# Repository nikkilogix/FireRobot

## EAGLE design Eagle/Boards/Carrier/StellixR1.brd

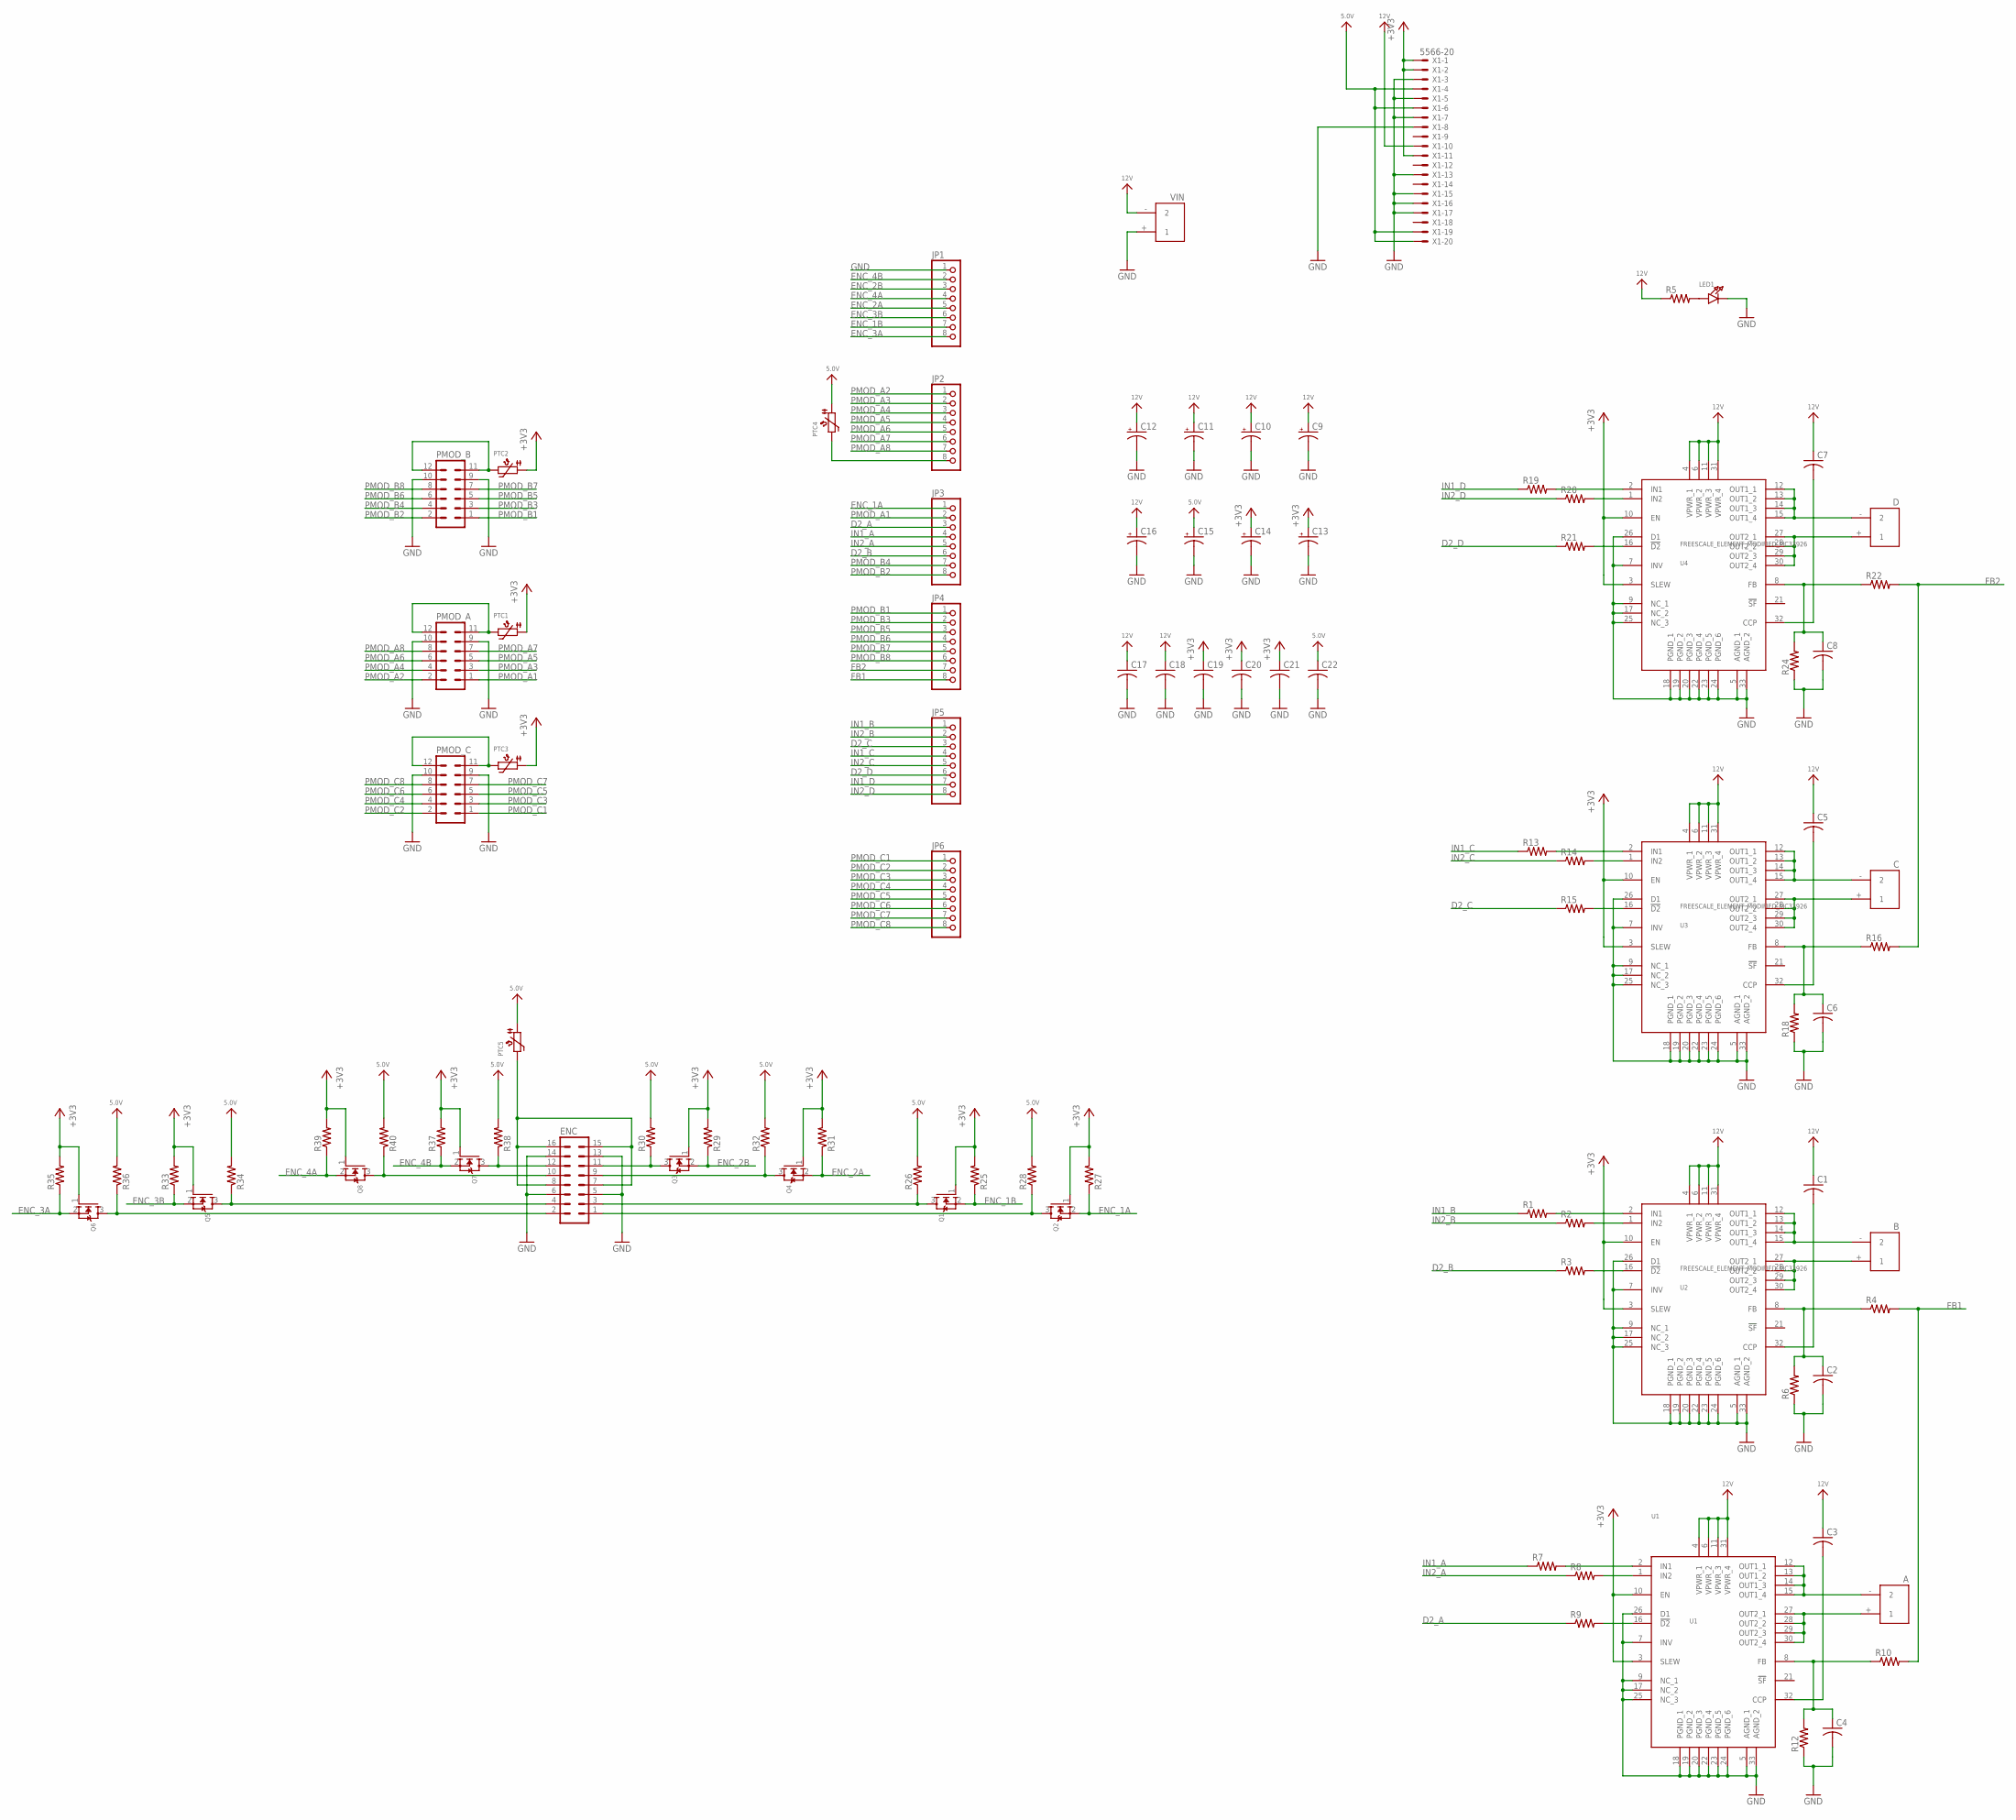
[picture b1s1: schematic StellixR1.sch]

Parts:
A: XT60_FEMALE
B: XT60_FEMALE
C: XT60_FEMALE
C1, C2, C3, C4, C5, C6, C7, C8, C17, C18, C19, C20, C21, C22: C-USC0805; C0805
C9, C10, C11, C12, C13, C14, C15, C16: CPOL-US153CLV-0605; 153CLV-0605
D: XT60_FEMALE
ENC: MA08-2
JP1, JP2, JP3, JP4, JP5, JP6: HEADER-1X8ROUND; 1X08_ROUND
LED1: LED0805_NOOUTLINE; CHIPLED_0805_NOOUTLINE
PMOD_A: MA06-2
PMOD_B: MA06-2
PMOD_C: MA06-2
PTC1, PTC2, PTC3, PTC4, PTC5: PTC1812
Q1, Q2, Q3, Q4, Q5, Q6, Q7, Q8: MOSFET-NWIDE; SOT23-WIDE
R1, R2, R3, R4, R5, R6, R7, R8, R9, R10, R12, R13, R14, R15, R16, R18, R19, R20, R21, R22, R24, R25, R26, R27, R28, R29, R30, R31, R32, R33, R34, R35, R36, R37, R38, R39, R40: R-US_R0805; R0805
U1: U1; FREESCALE_ELEMENT_MODIFIED_PQFN32_0P8_8X8_SLUG
U2, U3, U4: FREESCALE_ELEMENT_MODIFIED_MC33926; FREESCALE_ELEMENT_MODIFIED_PQFN32_0P8_8X8_SLUG
VIN: XT60_FEMALE
X1: 5566-20

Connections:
5.0V: C15.+, C22.1, PTC4.P$1 (1), PTC5.P$1 (1), R26.2, R28.2, R30.2, R32.2, R34.2, R36.2, R38.2, R40.2, X1.4, X1.6, X1.19, X1.20
12V: C1.1, C3.1, C5.1, C7.1, C9.+, C10.+, C11.+, C12.+, C16.+, C17.1, C18.1, R5.1, U1.4 (VPWR_1), U1.6 (VPWR_2), U1.11 (VPWR_3), U1.31 (VPWR_4), U2.4 (VPWR_1), U2.6 (VPWR_2), U2.11 (VPWR_3), U2.31 (VPWR_4), U3.4 (VPWR_1), U3.6 (VPWR_2), U3.11 (VPWR_3), U3.31 (VPWR_4), U4.4 (VPWR_1), U4.6 (VPWR_2), U4.11 (VPWR_3), U4.31 (VPWR_4), VIN.- (2), X1.10
+3V3: C13.+, C14.+, C19.1, C20.1, C21.1, PTC1.P$1 (1), PTC2.P$1 (1), PTC3.P$1 (1), Q1.1 (G), Q2.1 (G), Q3.1 (G), Q4.1 (G), Q5.1 (G), Q6.1 (G), Q7.1 (G), Q8.1 (G), R25.2, R27.2, R29.2, R31.2, R33.2, R35.2, R37.2, R39.2, U1.3 (SLEW), U1.10 (EN), U2.3 (SLEW), U2.10 (EN), U3.3 (SLEW), U3.10 (EN), U4.3 (SLEW), U4.10 (EN), X1.1, X1.2, X1.11
D2_A: JP3.3, R9.1
D2_B: JP3.6, R3.1
D2_C: JP5.3, R15.1
D2_D: JP5.6, R21.1
ENC_1A: JP3.1, Q2.2 (S), R27.1
ENC_1B: JP1.7, Q1.2 (S), R25.1
ENC_2A: JP1.5, Q4.2 (S), R31.1
ENC_2B: JP1.3, Q3.2 (S), R29.1
ENC_3A: JP1.8, Q6.2 (S), R35.1
ENC_3B: JP1.6, Q5.2 (S), R33.1
ENC_4A: JP1.4, Q8.2 (S), R39.1
ENC_4B: JP1.2, Q7.2 (S), R37.1
FB1: JP4.8, R4.2, R10.2
FB2: JP4.7, R16.2, R22.2
GND: C2.2, C4.2, C6.2, C8.2, C9.-, C10.-, C11.-, C12.-, C13.-, C14.-, C15.-, C16.-, C17.2, C18.2, C19.2, C20.2, C21.2, C22.2, ENC.5, ENC.6, ENC.13, ENC.14, JP1.1, LED1.C, PMOD_A.9, PMOD_A.10, PMOD_B.9, PMOD_B.10, PMOD_C.9, PMOD_C.10, R6.1, R12.1, R18.1, R24.1, U1.5 (AGND_1), U1.7 (INV), U1.9 (NC_1), U1.17 (NC_2), U1.18 (PGND_1), U1.19 (PGND_2), U1.20 (PGND_3), U1.22 (PGND_4), U1.23 (PGND_5), U1.24 (PGND_6), U1.25 (NC_3), U1.26 (D1), U1.33 (AGND_2), U2.5 (AGND_1), U2.7 (INV), U2.9 (NC_1), U2.17 (NC_2), U2.18 (PGND_1), U2.19 (PGND_2), U2.20 (PGND_3), U2.22 (PGND_4), U2.23 (PGND_5), U2.24 (PGND_6), U2.25 (NC_3), U2.26 (D1), U2.33 (AGND_2), U3.5 (AGND_1), U3.7 (INV), U3.9 (NC_1), U3.17 (NC_2), U3.18 (PGND_1), U3.19 (PGND_2), U3.20 (PGND_3), U3.22 (PGND_4), U3.23 (PGND_5), U3.24 (PGND_6), U3.25 (NC_3), U3.26 (D1), U3.33 (AGND_2), U4.5 (AGND_1), U4.7 (INV), U4.9 (NC_1), U4.17 (NC_2), U4.18 (PGND_1), U4.19 (PGND_2), U4.20 (PGND_3), U4.22 (PGND_4), U4.23 (PGND_5), U4.24 (PGND_6), U4.25 (NC_3), U4.26 (D1), U4.33 (AGND_2), VIN.+ (1), X1.3, X1.5, X1.7, X1.8, X1.13, X1.15, X1.16, X1.17
IN1_A: JP3.4, R7.1
IN1_B: JP5.1, R1.1
IN1_C: JP5.4, R13.1
IN1_D: JP5.7, R19.1
IN2_A: JP3.5, R8.1
IN2_B: JP5.2, R2.1
IN2_C: JP5.5, R14.1
IN2_D: JP5.8, R20.1
MOUTA: B.- (2), U2.12 (OUT1_1), U2.13 (OUT1_2), U2.14 (OUT1_3), U2.15 (OUT1_4)
MOUTB: B.+ (1), U2.27 (OUT2_1), U2.28 (OUT2_2), U2.29 (OUT2_3), U2.30 (OUT2_4)
unnamed: R3.2, U2.16 (!D2)
unnamed: JP2.8, PTC4.P$2 (2)
unnamed: PMOD_A.11, PMOD_A.12, PTC1.P$2 (2)
unnamed: R8.2, U1.1 (IN2)
unnamed: PMOD_C.11, PMOD_C.12, PTC3.P$2 (2)
unnamed: R2.2, U2.1 (IN2)
unnamed: R1.2, U2.2 (IN1)
unnamed: ENC.1, Q2.3 (D), R28.1
unnamed: ENC.4, Q5.3 (D), R34.1
unnamed: R7.2, U1.2 (IN1)
unnamed: PMOD_B.11, PMOD_B.12, PTC2.P$2 (2)
unnamed: C1.2, U2.32 (CCP)
unnamed: A.- (2), U1.12 (OUT1_1), U1.13 (OUT1_2), U1.14 (OUT1_3), U1.15 (OUT1_4)
unnamed: C2.1, R4.1, R6.2, U2.8 (FB)
unnamed: ENC.7, ENC.8, ENC.15, ENC.16, PTC5.P$2 (2)
unnamed: LED1.A, R5.2
unnamed: A.+ (1), U1.27 (OUT2_1), U1.28 (OUT2_2), U1.29 (OUT2_3), U1.30 (OUT2_4)
unnamed: C3.2, U1.32 (CCP)
unnamed: R9.2, U1.16 (!D2)
unnamed: C4.1, R10.1, R12.2, U1.8 (FB)
unnamed: R14.2, U3.1 (IN2)
unnamed: R13.2, U3.2 (IN1)
unnamed: C.- (2), U3.12 (OUT1_1), U3.13 (OUT1_2), U3.14 (OUT1_3), U3.15 (OUT1_4)
unnamed: C.+ (1), U3.27 (OUT2_1), U3.28 (OUT2_2), U3.29 (OUT2_3), U3.30 (OUT2_4)
unnamed: C5.2, U3.32 (CCP)
unnamed: R15.2, U3.16 (!D2)
unnamed: C6.1, R16.1, R18.2, U3.8 (FB)
unnamed: R20.2, U4.1 (IN2)
unnamed: R19.2, U4.2 (IN1)
unnamed: D.- (2), U4.12 (OUT1_1), U4.13 (OUT1_2), U4.14 (OUT1_3), U4.15 (OUT1_4)
unnamed: D.+ (1), U4.27 (OUT2_1), U4.28 (OUT2_2), U4.29 (OUT2_3), U4.30 (OUT2_4)
unnamed: C7.2, U4.32 (CCP)
unnamed: R21.2, U4.16 (!D2)
unnamed: C8.1, R22.1, R24.2, U4.8 (FB)
unnamed: ENC.3, Q1.3 (D), R26.1
unnamed: ENC.2, Q6.3 (D), R36.1
unnamed: ENC.11, Q3.3 (D), R30.1
unnamed: ENC.9, Q4.3 (D), R32.1
unnamed: ENC.12, Q7.3 (D), R38.1
unnamed: ENC.10, Q8.3 (D), R40.1
PMOD_A1: JP3.2, PMOD_A.1
PMOD_A2: JP2.1, PMOD_A.2
PMOD_A3: JP2.2, PMOD_A.3
PMOD_A4: JP2.3, PMOD_A.4
PMOD_A5: JP2.4, PMOD_A.5
PMOD_A6: JP2.5, PMOD_A.6
PMOD_A7: JP2.6, PMOD_A.7
PMOD_A8: JP2.7, PMOD_A.8
PMOD_B1: JP4.1, PMOD_B.1
PMOD_B2: JP3.8, PMOD_B.2
PMOD_B3: JP4.2, PMOD_B.3
PMOD_B4: JP3.7, PMOD_B.4
PMOD_B5: JP4.3, PMOD_B.5
PMOD_B6: JP4.4, PMOD_B.6
PMOD_B7: JP4.5, PMOD_B.7
PMOD_B8: JP4.6, PMOD_B.8
PMOD_C1: JP6.1, PMOD_C.1
PMOD_C2: JP6.2, PMOD_C.2
PMOD_C3: JP6.3, PMOD_C.3
PMOD_C4: JP6.4, PMOD_C.4
PMOD_C5: JP6.5, PMOD_C.5
PMOD_C6: JP6.6, PMOD_C.6
PMOD_C7: JP6.7, PMOD_C.7
PMOD_C8: JP6.8, PMOD_C.8

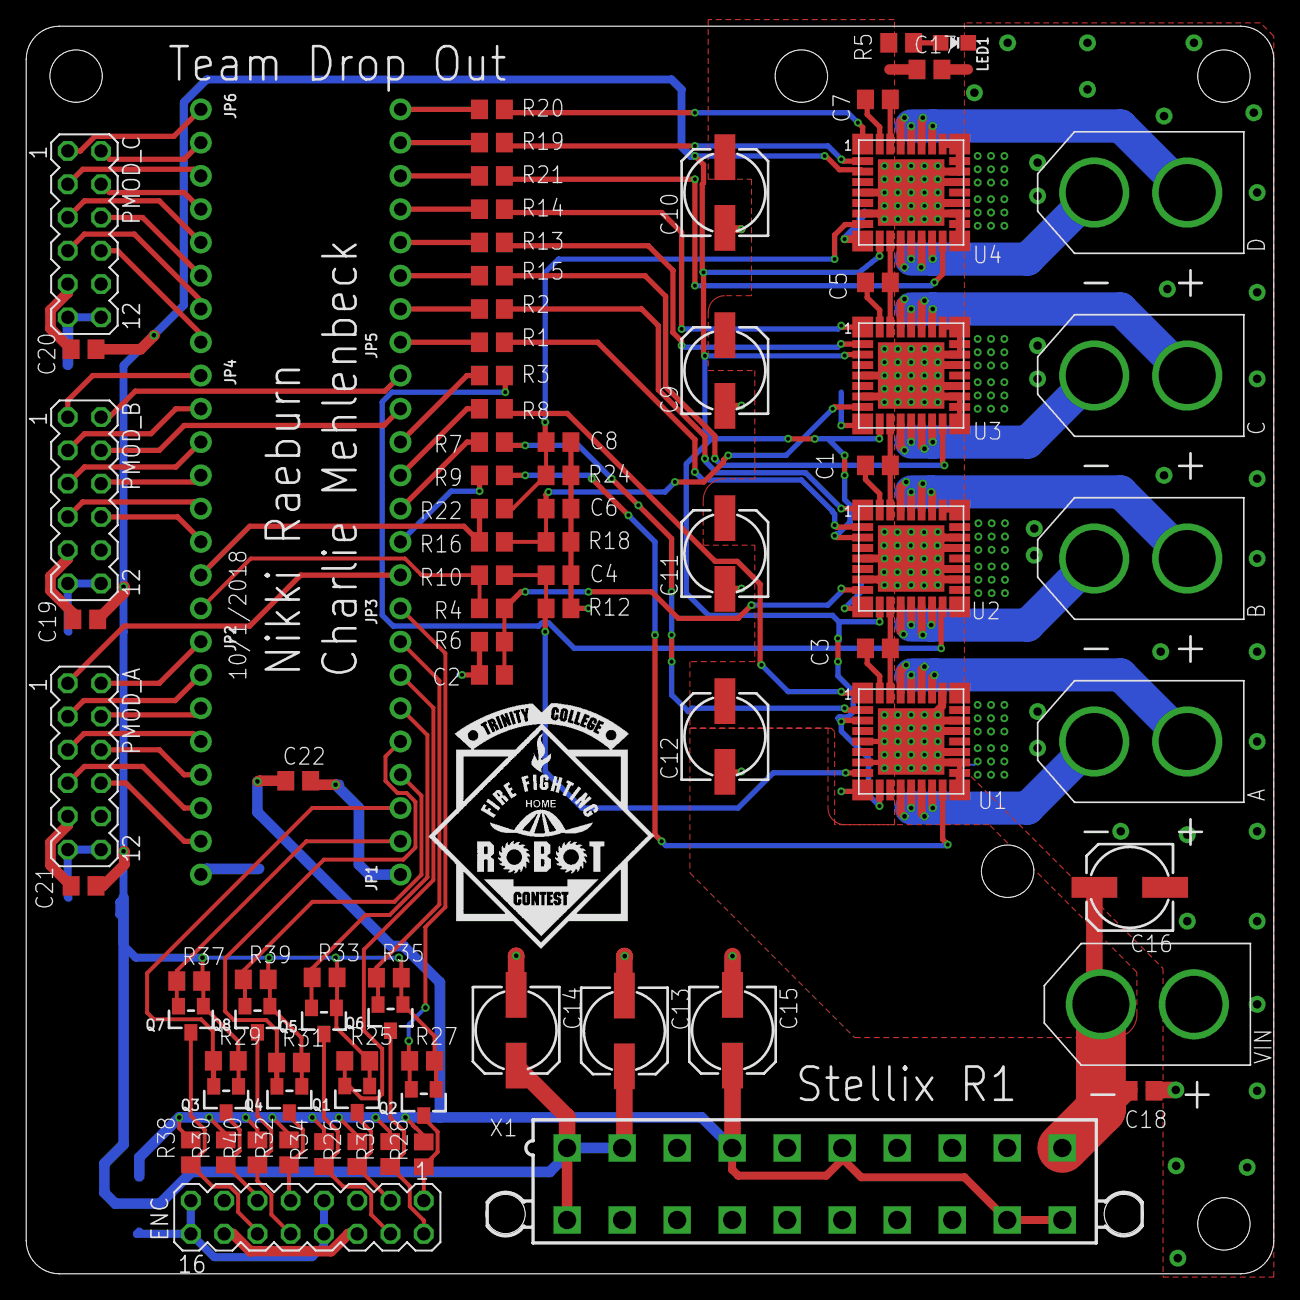
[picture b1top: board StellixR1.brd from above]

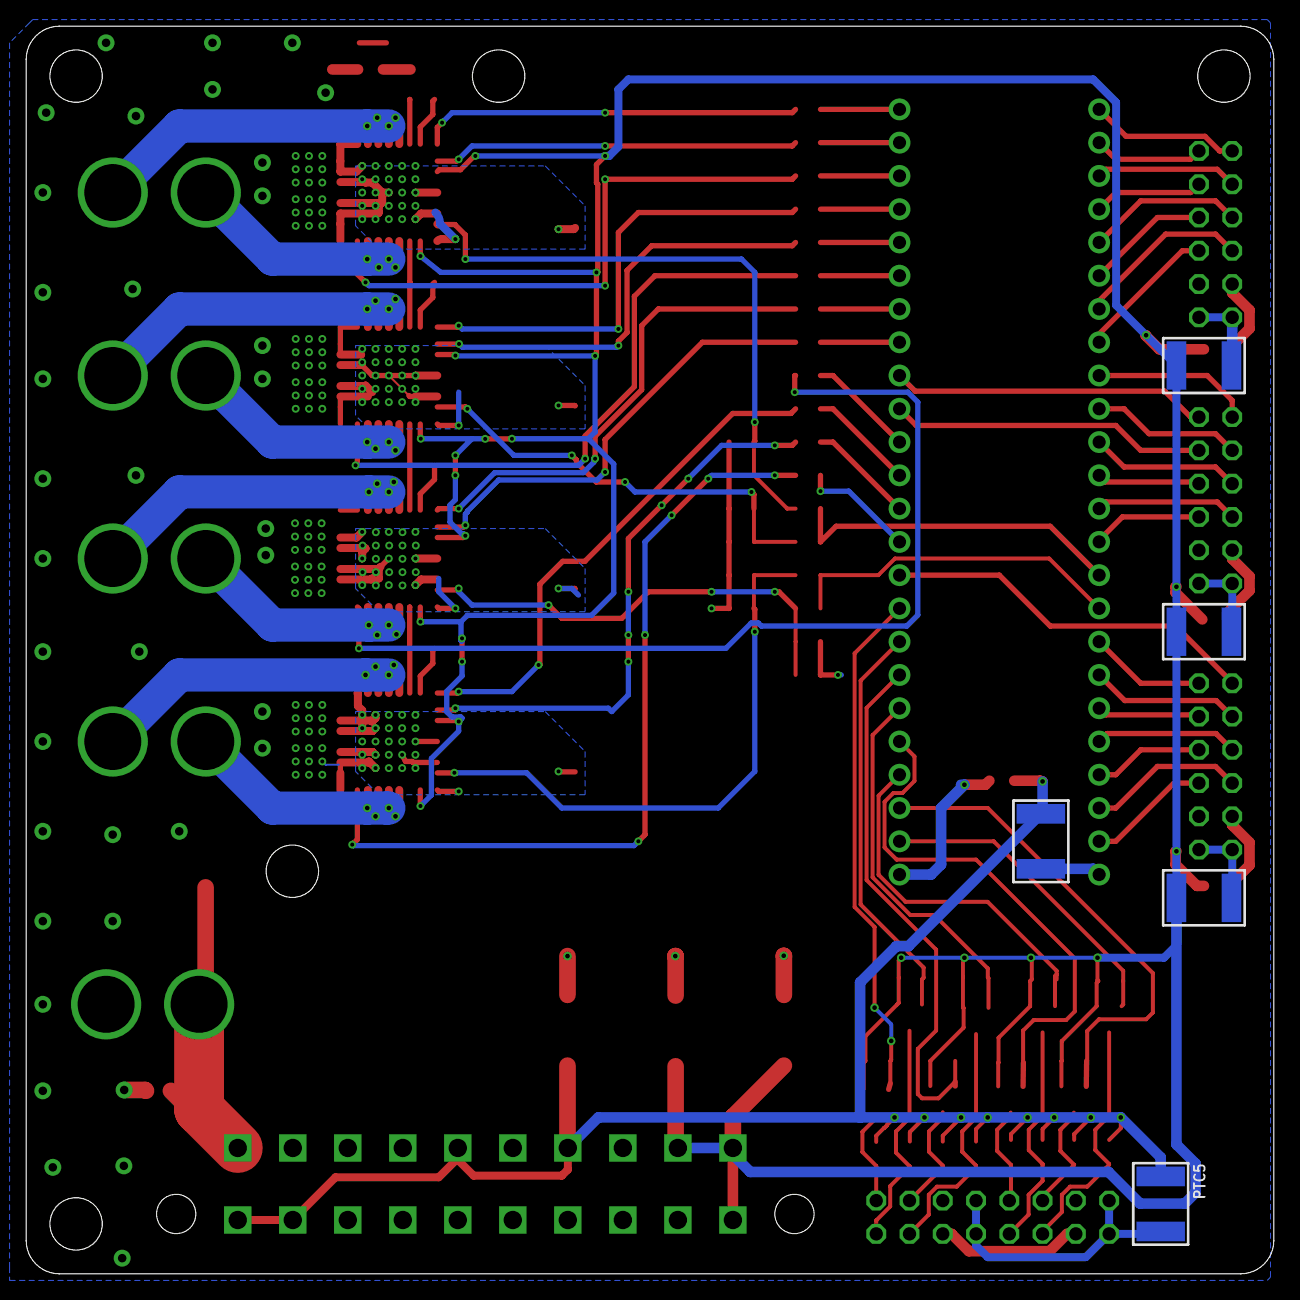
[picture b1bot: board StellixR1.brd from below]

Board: 2 copper layers, 95.2 x 95.2 mm, 93 parts (5 on the bottom side), 92 nets.

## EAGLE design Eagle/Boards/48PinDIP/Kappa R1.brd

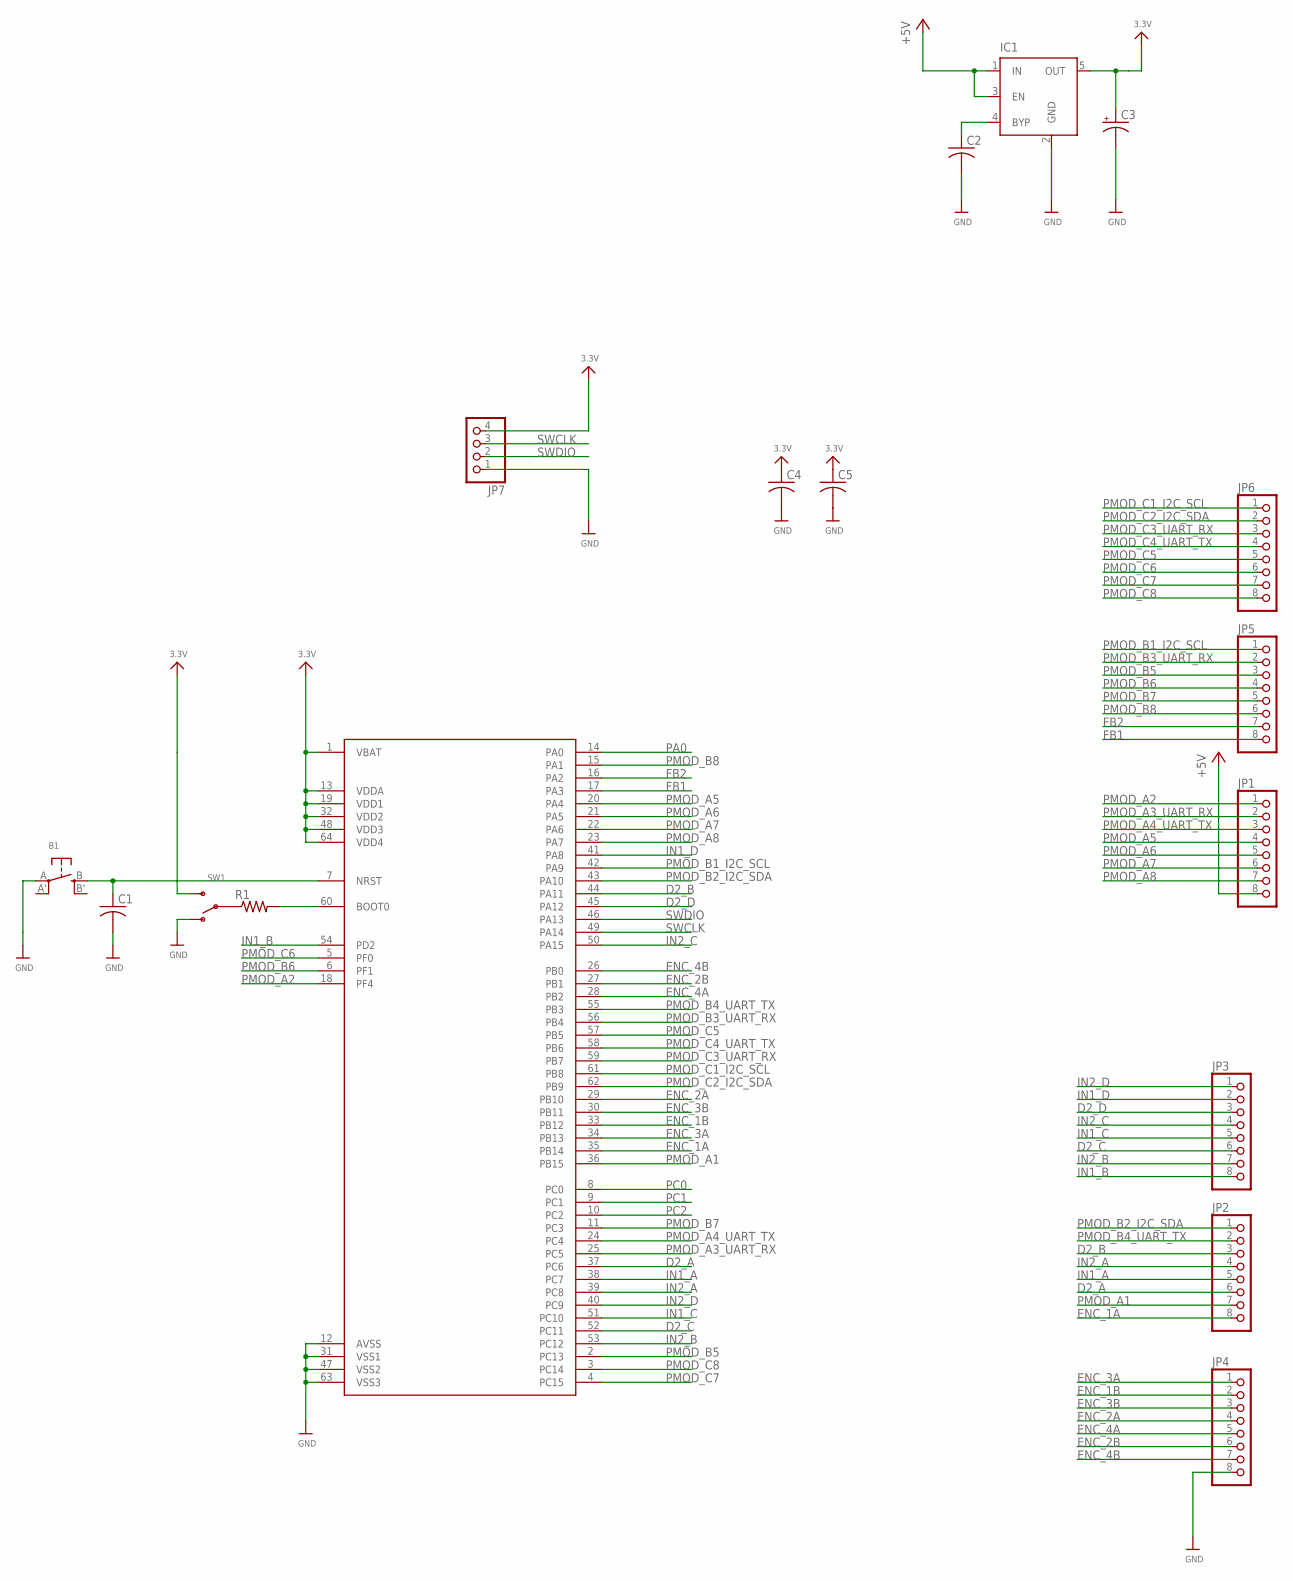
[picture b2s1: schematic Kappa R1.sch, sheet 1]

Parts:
B1: SWITCH_TACT_SMT4.6X2.8; BTN_KMR2_4.6X2.8
C1, C2: C-USC0805K; C0805K
C3: CPOL-USCT3216; CT3216
C4, C5: C-USC0805; C0805
IC1: MIC5219XX; SOT23-5
JP1, JP2, JP3, JP4, JP5, JP6: HEADER-1X8ROUND; 1X08_ROUND
JP7: HEADER-1X4ROUND; 1X04_ROUND
R1: R-US_R0805; R0805
SW1: SWITCH_SPDT; SPDT_SMT_SSSS811101
U$1: STM32F303; LQFP64

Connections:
3.3V: C3.- (+), C4.1, C5.1, IC1.5 (OUT), JP7.4, SW1.C (S), U$1.1 (VBAT), U$1.13 (VDDA), U$1.19 (VDD1), U$1.32 (VDD2), U$1.48 (VDD3), U$1.64 (VDD4)
+5V: IC1.1 (IN), IC1.3 (EN), JP1.8
D2_A: JP2.6, U$1.37 (PC6)
D2_B: JP2.3, U$1.44 (PA11)
D2_C: JP3.6, U$1.52 (PC11)
D2_D: JP3.3, U$1.45 (PA12)
ENC_1A: JP2.8, U$1.35 (PB14)
ENC_1B: JP4.2, U$1.33 (PB12)
ENC_2A: JP4.4, U$1.29 (PB10)
ENC_2B: JP4.6, U$1.27 (PB1)
ENC_3A: JP4.1, U$1.34 (PB13)
ENC_3B: JP4.3, U$1.30 (PB11)
ENC_4A: JP4.5, U$1.28 (PB2)
ENC_4B: JP4.7, U$1.26 (PB0)
FB1: JP5.8, U$1.17 (PA3)
FB2: JP5.7, U$1.16 (PA2)
GND: B1.A, C1.2, C2.2, C3.+ (-), C4.2, C5.2, IC1.2 (GND), JP4.8, JP7.1, SW1.A (O), U$1.12 (AVSS), U$1.31 (VSS1), U$1.47 (VSS2), U$1.63 (VSS3)
IN1_A: JP2.5, U$1.38 (PC7)
IN1_B: JP3.8, U$1.54 (PD2)
IN1_C: JP3.5, U$1.51 (PC10)
IN1_D: JP3.2, U$1.41 (PA8)
IN2_A: JP2.4, U$1.39 (PC8)
IN2_B: JP3.7, U$1.53 (PC12)
IN2_C: JP3.4, U$1.50 (PA15)
IN2_D: JP3.1, U$1.40 (PC9)
unnamed: R1.2, U$1.60 (BOOT0)
unnamed: B1.B (S), C1.1, U$1.7 (NRST)
unnamed: R1.1, SW1.B
unnamed: C2.1, IC1.4 (BYP)
PA0: U$1.14 (PA0)
PC0: U$1.8 (PC0)
PC1: U$1.9 (PC1)
PC2: U$1.10 (PC2)
PMOD_A1: JP2.7, U$1.36 (PB15)
PMOD_A2: JP1.1, U$1.18 (PF4)
PMOD_A3_UART_RX: JP1.2, U$1.25 (PC5)
PMOD_A4_UART_TX: JP1.3, U$1.24 (PC4)
PMOD_A5: JP1.4, U$1.20 (PA4)
PMOD_A6: JP1.5, U$1.21 (PA5)
PMOD_A7: JP1.6, U$1.22 (PA6)
PMOD_A8: JP1.7, U$1.23 (PA7)
PMOD_B1_I2C_SCL: JP5.1, U$1.42 (PA9)
PMOD_B2_I2C_SDA: JP2.1, U$1.43 (PA10)
PMOD_B3_UART_RX: JP5.2, U$1.56 (PB4)
PMOD_B4_UART_TX: JP2.2, U$1.55 (PB3)
PMOD_B5: JP5.3, U$1.2 (PC13)
PMOD_B6: JP5.4, U$1.6 (PF1)
PMOD_B7: JP5.5, U$1.11 (PC3)
PMOD_B8: JP5.6, U$1.15 (PA1)
PMOD_C1_I2C_SCL: JP6.1, U$1.61 (PB8)
PMOD_C2_I2C_SDA: JP6.2, U$1.62 (PB9)
PMOD_C3_UART_RX: JP6.3, U$1.59 (PB7)
PMOD_C4_UART_TX: JP6.4, U$1.58 (PB6)
PMOD_C5: JP6.5, U$1.57 (PB5)
PMOD_C6: JP6.6, U$1.5 (PF0)
PMOD_C7: JP6.7, U$1.4 (PC15)
PMOD_C8: JP6.8, U$1.3 (PC14)
SWCLK: JP7.3, U$1.49 (PA14)
SWDIO: JP7.2, U$1.46 (PA13)

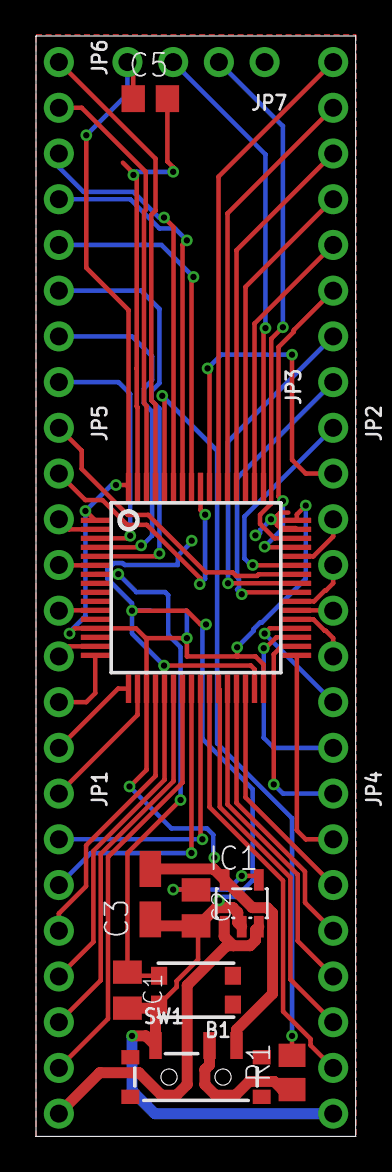
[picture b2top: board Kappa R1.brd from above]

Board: 2 copper layers, 17.8 x 61.1 mm, 17 parts (1 on the bottom side), 55 nets.

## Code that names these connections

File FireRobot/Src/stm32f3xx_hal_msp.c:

/**
  ******************************************************************************
  * File Name          : stm32f3xx_hal_msp.c
  * Description        : This file provides code for the MSP Initialization 
  *                      and de-Initialization codes.
  ******************************************************************************
  ** This notice applies to any and all portions of this file
  * that are not between comment pairs USER CODE BEGIN and
  * USER CODE END. Other portions of this file, whether 
  * inserted by the user or by software development tools
  * are owned by their respective copyright owners.
  *
  * COPYRIGHT(c) 2018 STMicroelectronics
  *
  * Redistribution and use in source and binary forms, with or without modification,
  * are permitted provided that the following conditions are met:
  *   1. Redistributions of source code must retain the above copyright notice,
  *      this list of conditions and the following disclaimer.
  *   2. Redistributions in binary form must reproduce the above copyright notice,
  *      this list of conditions and the following disclaimer in the documentation
  *      and/or other materials provided with the distribution.
  *   3. Neither the name of STMicroelectronics nor the names of its contributors
  *      may be used to endorse or promote products derived from this software
  *      without specific prior written permission.
  *
  * THIS SOFTWARE IS PROVIDED BY THE COPYRIGHT HOLDERS AND CONTRIBUTORS "AS IS"
  * AND ANY EXPRESS OR IMPLIED WARRANTIES, INCLUDING, BUT NOT LIMITED TO, THE
  * IMPLIED WARRANTIES OF MERCHANTABILITY AND FITNESS FOR A PARTICULAR PURPOSE ARE
  * DISCLAIMED. IN NO EVENT SHALL THE COPYRIGHT HOLDER OR CONTRIBUTORS BE LIABLE
  * FOR ANY DIRECT, INDIRECT, INCIDENTAL, SPECIAL, EXEMPLARY, OR CONSEQUENTIAL
  * DAMAGES (INCLUDING, BUT NOT LIMITED TO, PROCUREMENT OF SUBSTITUTE GOODS OR
  * SERVICES; LOSS OF USE, DATA, OR PROFITS; OR BUSINESS INTERRUPTION) HOWEVER
  * CAUSED AND ON ANY THEORY OF LIABILITY, WHETHER IN CONTRACT, STRICT LIABILITY,
  * OR TORT (INCLUDING NEGLIGENCE OR OTHERWISE) ARISING IN ANY WAY OUT OF THE USE
  * OF THIS SOFTWARE, EVEN IF ADVISED OF THE POSSIBILITY OF SUCH DAMAGE.
  *
  ******************************************************************************
  */
/* Includes ------------------------------------------------------------------*/
#include "stm32f3xx_hal.h"
extern void _Error_Handler(char *, int);
/* USER CODE BEGIN 0 */

/* USER CODE END 0 */
/**
  * Initializes the Global MSP.
  */
void HAL_MspInit(void)
{
  /* USER CODE BEGIN MspInit 0 */

  /* USER CODE END MspInit 0 */

  __HAL_RCC_SYSCFG_CLK_ENABLE();
  __HAL_RCC_PWR_CLK_ENABLE();

  HAL_NVIC_SetPriorityGrouping(NVIC_PRIORITYGROUP_0);

  /* System interrupt init*/
  /* MemoryManagement_IRQn interrupt configuration */
  HAL_NVIC_SetPriority(MemoryManagement_IRQn, 0, 0);
  /* BusFault_IRQn interrupt configuration */
  HAL_NVIC_SetPriority(BusFault_IRQn, 0, 0);
  /* UsageFault_IRQn interrupt configuration */
  HAL_NVIC_SetPriority(UsageFault_IRQn, 0, 0);
  /* SVCall_IRQn interrupt configuration */
  HAL_NVIC_SetPriority(SVCall_IRQn, 0, 0);
  /* DebugMonitor_IRQn interrupt configuration */
  HAL_NVIC_SetPriority(DebugMonitor_IRQn, 0, 0);
  /* PendSV_IRQn interrupt configuration */
  HAL_NVIC_SetPriority(PendSV_IRQn, 0, 0);
  /* SysTick_IRQn interrupt configuration */
  HAL_NVIC_SetPriority(SysTick_IRQn, 0, 0);

  /* USER CODE BEGIN MspInit 1 */

  /* USER CODE END MspInit 1 */
}

void HAL_I2C_MspInit(I2C_HandleTypeDef* hi2c)
{

  GPIO_InitTypeDef GPIO_InitStruct;
  if(hi2c->Instance==I2C1)
  {
  /* USER CODE BEGIN I2C1_MspInit 0 */

  /* USER CODE END I2C1_MspInit 0 */
  
    /**I2C1 GPIO Configuration    
    PB6     ------> I2C1_SCL
    PB7     ------> I2C1_SDA 
    */
    GPIO_InitStruct.Pin = I2C1_SCL_Pin|I2C1_SDA_Pin;
    GPIO_InitStruct.Mode = GPIO_MODE_AF_OD;
    GPIO_InitStruct.Pull = GPIO_PULLUP;
    GPIO_InitStruct.Speed = GPIO_SPEED_FREQ_HIGH;
    GPIO_InitStruct.Alternate = GPIO_AF4_I2C1;
    HAL_GPIO_Init(GPIOB, &GPIO_InitStruct);

    /* Peripheral clock enable */
    __HAL_RCC_I2C1_CLK_ENABLE();
  /* USER CODE BEGIN I2C1_MspInit 1 */

  /* USER CODE END I2C1_MspInit 1 */
  }

}

void HAL_I2C_MspDeInit(I2C_HandleTypeDef* hi2c)
{

  if(hi2c->Instance==I2C1)
  {
  /* USER CODE BEGIN I2C1_MspDeInit 0 */

  /* USER CODE END I2C1_MspDeInit 0 */
    /* Peripheral clock disable */
    __HAL_RCC_I2C1_CLK_DISABLE();
  
    /**I2C1 GPIO Configuration    
    PB6     ------> I2C1_SCL
    PB7     ------> I2C1_SDA 
    */
    HAL_GPIO_DeInit(GPIOB, I2C1_SCL_Pin|I2C1_SDA_Pin);

  /* USER CODE BEGIN I2C1_MspDeInit 1 */

  /* USER CODE END I2C1_MspDeInit 1 */
  }

}

void HAL_SPI_MspInit(SPI_HandleTypeDef* hspi)
{

  GPIO_InitTypeDef GPIO_InitStruct;
  if(hspi->Instance==SPI1)
  {
  /* USER CODE BEGIN SPI1_MspInit 0 */

  /* USER CODE END SPI1_MspInit 0 */
    /* Peripheral clock enable */
    __HAL_RCC_SPI1_CLK_ENABLE();
  
    /**SPI1 GPIO Configuration    
    PA5     ------> SPI1_SCK
    PA6     ------> SPI1_MISO
    PA7     ------> SPI1_MOSI 
    */
    GPIO_InitStruct.Pin = SPI1_SCK_Pin|SPI1_MISO_Pin|SPI1_MISOA7_Pin;
    GPIO_InitStruct.Mode = GPIO_MODE_AF_PP;
    GPIO_InitStruct.Pull = GPIO_NOPULL;
    GPIO_InitStruct.Speed = GPIO_SPEED_FREQ_HIGH;
    GPIO_InitStruct.Alternate = GPIO_AF5_SPI1;
    HAL_GPIO_Init(GPIOA, &GPIO_InitStruct);

  /* USER CODE BEGIN SPI1_MspInit 1 */

  /* USER CODE END SPI1_MspInit 1 */
  }

}

void HAL_SPI_MspDeInit(SPI_HandleTypeDef* hspi)
{

  if(hspi->Instance==SPI1)
  {
  /* USER CODE BEGIN SPI1_MspDeInit 0 */

  /* USER CODE END SPI1_MspDeInit 0 */
    /* Peripheral clock disable */
    __HAL_RCC_SPI1_CLK_DISABLE();
  
    /**SPI1 GPIO Configuration    
    PA5     ------> SPI1_SCK
    PA6     ------> SPI1_MISO
    PA7     ------> SPI1_MOSI 
    */
    HAL_GPIO_DeInit(GPIOA, SPI1_SCK_Pin|SPI1_MISO_Pin|SPI1_MISOA7_Pin);

  /* USER CODE BEGIN SPI1_MspDeInit 1 */

  /* USER CODE END SPI1_MspDeInit 1 */
  }

}

void HAL_PCD_MspInit(PCD_HandleTypeDef* hpcd)
{

  GPIO_InitTypeDef GPIO_InitStruct;
  if(hpcd->Instance==USB)
  {
  /* USER CODE BEGIN USB_MspInit 0 */

  /* USER CODE END USB_MspInit 0 */
  
    /**USB GPIO Configuration    
    PA11     ------> USB_DM
    PA12     ------> USB_DP 
    */
    GPIO_InitStruct.Pin = DM_Pin|DP_Pin;
    GPIO_InitStruct.Mode = GPIO_MODE_AF_PP;
    GPIO_InitStruct.Pull = GPIO_NOPULL;
    GPIO_InitStruct.Speed = GPIO_SPEED_FREQ_HIGH;
    GPIO_InitStruct.Alternate = GPIO_AF14_USB;
    HAL_GPIO_Init(GPIOA, &GPIO_InitStruct);

    /* Peripheral clock enable */
    __HAL_RCC_USB_CLK_ENABLE();
  /* USER CODE BEGIN USB_MspInit 1 */

  /* USER CODE END USB_MspInit 1 */
  }

}

void HAL_PCD_MspDeInit(PCD_HandleTypeDef* hpcd)
{

  if(hpcd->Instance==USB)
  {
  /* USER CODE BEGIN USB_MspDeInit 0 */

  /* USER CODE END USB_MspDeInit 0 */
    /* Peripheral clock disable */
    __HAL_RCC_USB_CLK_DISABLE();
  
    /**USB GPIO Configuration    
    PA11     ------> USB_DM
    PA12     ------> USB_DP 
    */
    HAL_GPIO_DeInit(GPIOA, DM_Pin|DP_Pin);

  /* USER CODE BEGIN USB_MspDeInit 1 */

  /* USER CODE END USB_MspDeInit 1 */
  }

}

/* USER CODE BEGIN 1 */

/* USER CODE END 1 */

/**
  * @}
  */

/**
  * @}
  */

/************************ (C) COPYRIGHT STMicroelectronics *****END OF FILE****/

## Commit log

2018-11-12 Eagle Files Update
2018-11-12 Carrier

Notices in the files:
parts and their libraries:
microbuilder: This work is placed in the public domain, and may be freely used for commercial and non-commercial work with the following conditions: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
